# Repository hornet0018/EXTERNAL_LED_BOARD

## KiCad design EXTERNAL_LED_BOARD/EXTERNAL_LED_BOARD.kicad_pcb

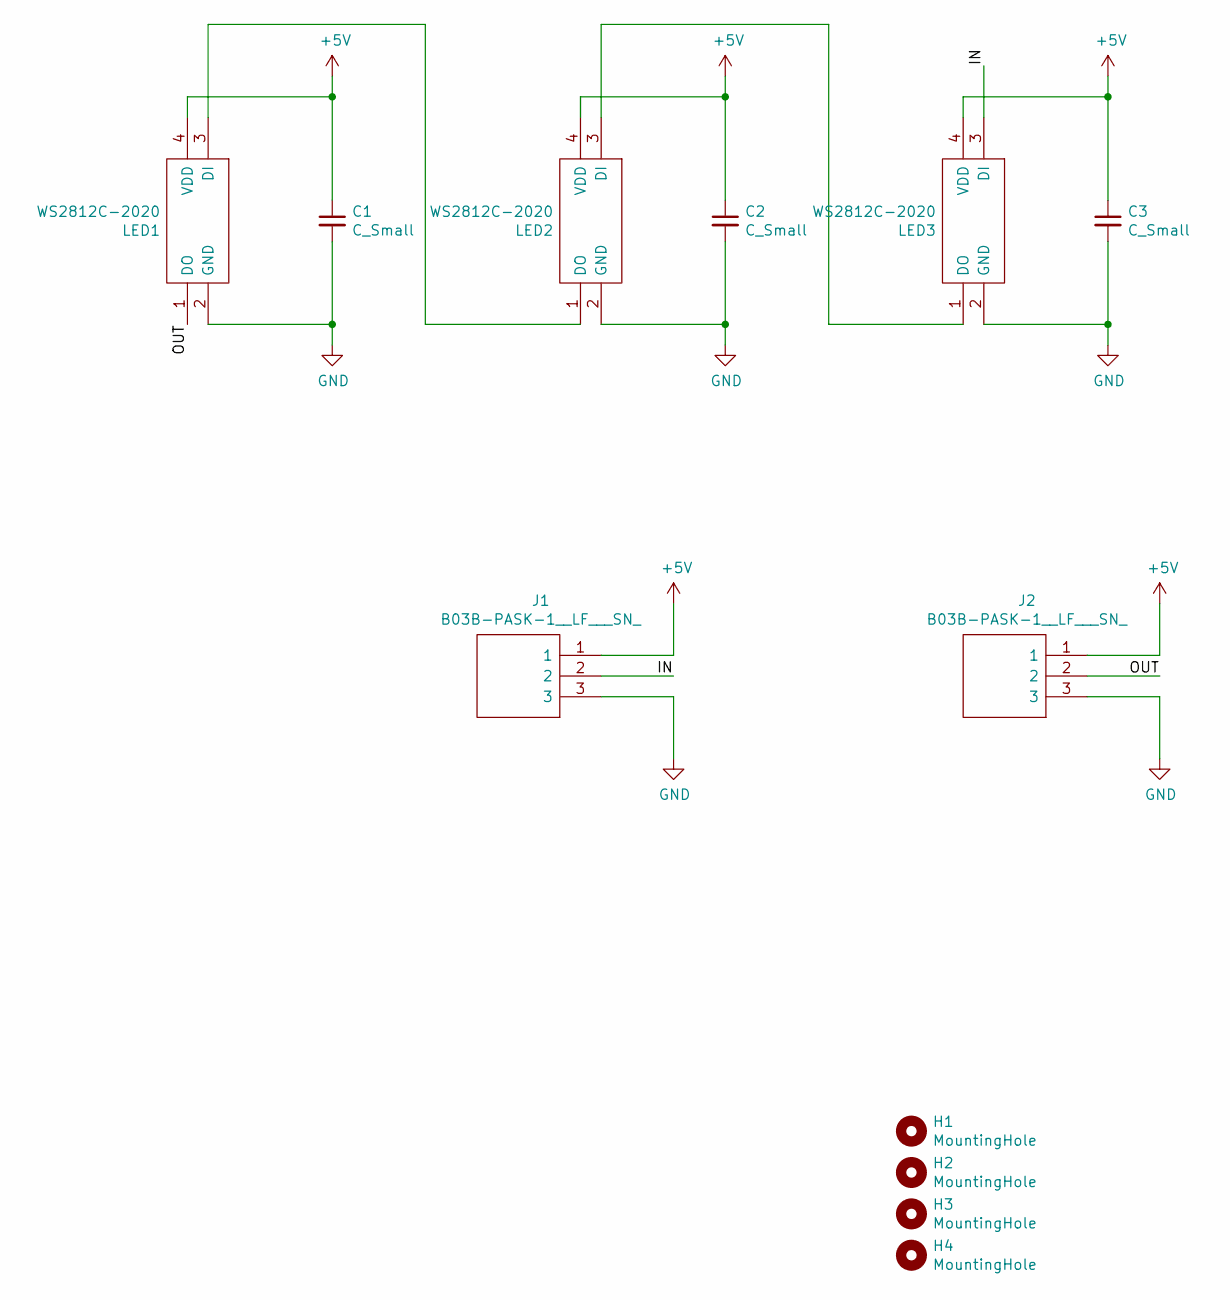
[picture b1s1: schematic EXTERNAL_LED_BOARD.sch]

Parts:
C1, C2, C3: C_Small; C_0603_1608Metric_Pad1.05x0.95mm_HandSolder
H1, H2, H3, H4: MountingHole; MountingHole_3.2mm_M3_DIN965_Pad_TopBottom
J1, J2: B03B-PASK-1__LF___SN_; B03BPASK1LFSN; Manufacturer_Part_Number B03B-PASK-1 (LF) (SN)
LED1, LED2, LED3: WS2812C-2020; WS2812C2020; Manufacturer_Part_Number WS2812C-2020

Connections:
+5V: C1.1, C2.1, C3.1, J1.1, J2.1, LED1.4 (VDD), LED2.4 (VDD), LED3.4 (VDD)
/IN: J1.2, LED3.3 (DI)
/OUT: J2.2, LED1.1 (DO)
GND: C1.2, C2.2, C3.2, J1.3, J2.3, LED1.2 (GND), LED2.2 (GND), LED3.2 (GND)
unnamed: LED1.3 (DI), LED2.1 (DO)
unnamed: LED2.3 (DI), LED3.1 (DO)

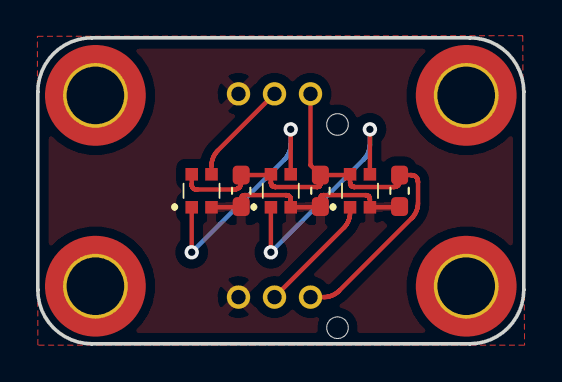
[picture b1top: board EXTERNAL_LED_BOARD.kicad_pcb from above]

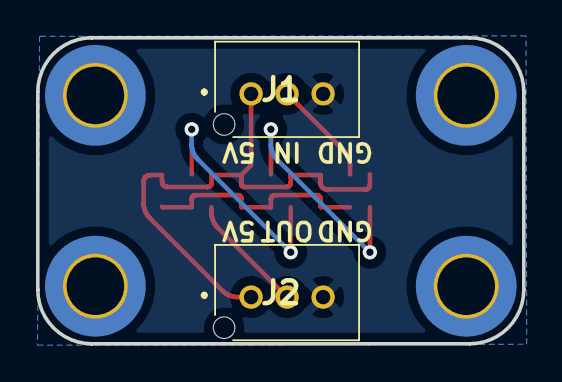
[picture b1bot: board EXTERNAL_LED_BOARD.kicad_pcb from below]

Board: 2 copper layers, 27.0 x 17.0 mm, 12 parts (2 on the bottom side), 6 nets.
